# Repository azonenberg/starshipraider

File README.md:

# Intro

This is the umbrella repo for a lot of my T&M projects. Some will end up in separate repos.

# Project Codenames

Boards, subsystems, etc are all named after famous electrical engineers who made major contributions to the field of test equipment design.

# Platform Architecture

All instruments are planned to share the same basic platform. Generally speaking, this platform will be:

## Mechanical form factor

* 1U rackmount, depth dependent on the specific instrument.

## Power
* 48V DC power on 6-pin Molex Mini-Fit Jr connector (back left)
* Intermediate bus converter based on the [trigger crossbar](https://github.com/azonenberg/triggercrossbar/tree/main/pcb/ibc) IBC design to produce 12V output.
* Possible changes from current design (as of 2024-03-31): switch to bigger MCU with flash space for A/B firmware images, consider swapping main DC-DC module to something with lower standby power (current IBC wastes ~3W no-load which isn't great)
* STM32L0 based power/reset sequencing supervisor with soft power on/off

## Software/firmware stack

* ngscopeclient as primary UI
* staticnet as TCP/IP stack
* Bare metal, no OS, no dynamic memory allocation
* SFTP based firmware update, eventually with signed updates (user can add new signing keys via uart console)

## Main chipset
* STM32H7 as main processor running SCPI stack, sshd, and control plane functionality (low speed ADCs/DACs, GPIOs, etc)
* Xilinx UltraScale+ / UltraScale / 7 series FPGA as main datapath. Some instruments may have >1 FPGA.

## Communications

* KSZ9031 based 10/100/1000 baseT fallback Ethernet interface
* 10Gbase-R SFP+ / 25Gbase-R SFP28 interface for primary remote control path
* Twinlan transport, SCPI control plane socket plus bare TCP socket for binary waveform data
* 2.13" monochrome e-ink display with IP/version/status information
* RS232 console on rear panel RJ45 (Cisco pinout)

## RF / signal interface

* Front panel SMA/BNC probe ports. Number of channels dependent on PCB size.
* Rear panel SMA for 10 MHz reference in, level TBD
* May have reference out TBD
* May have PPS in/out TBD
* Rear panel trigger in/out if applicable

# Roadmap (including external repos)

1. [Trigger Crossbar](https://github.com/azonenberg/triggercrossbar)  
Currently in progress. Not planning to make in volume, focus is on prototyping as much of the platform as possible to speed development and de-risk future projects. Prototype assembled, firmware dev in progress.

1. [kup-lulz](https://github.com/azonenberg/misc-devboards/tree/master/kup-lulz): One-off Kintex UltraScale+ test board on OSHPark 4 layers, using a sketchy reballed aliexpress FPGA. Intended as a low-risk validation for UltraScale+ based power, pcb footprint/schematic, and some RTL development. Schematic complete, fine tuning layout.

1. [GROVER](https://github.com/azonenberg/grover): Kintex UltraScale+ based 10/25G BERT. On hold until kup-lulz is brought up and working as it will essentially be a scaled-up version of the same design

1. VOLLUM (Howard Vollum, co-inventor of triggered-sweep oscilloscope)
    - No design progress yet, but can probably leverage some old frontend work. One 6 Gbps AD9213 is in inventory for a scaled down (7 series based) single channel prototype.
    - 2 GHz / 10 Gsps 12 bit oscilloscope, as many channels as I can fit in 1U
    - Per channel: 1x AD9213, frontend, XCAU25P-2FFVB676, 72-bit DDR4 LRDIMM
    - Top level: One more FPGA, details TBD, doing trigger sync and MSO channels
    - Will need to use parallel / bonded serial LVDS for waveform download since all 12 GTYs on the KU25Ps will be used for the JESD204

-----

# Stuff below here is way old and needs to be redone

-----

## General

* STARSHIPRAIDER: umbrella term for the entire project
* CLARKE (Edith Clarke, first female EE professor in USA): the original STARSHIPRAIDER project

## Oscilloscopes

All are 8 channels??

* BLONDEL (Andre-Eugene Blondel, inventor of electromechanical oscillograph) \
  8 bit: 100 MHz / 250 - 500 - 1000 Msps \
  12 bit: 50 MHz / 125 - 250 - 500 Msps \
  4 AFE : 1 HMCAD1520 \
  Two acquisition cards, 4 channels each \
  One XC7A100T-2FGG676 on main board \
  One DDR3 800 SODIMM on main board

* DUDDELL (William Duddell, inventor of moving-coil mirror oscillograph) \
  250 MHz / 1 Gsps, 1 AFE : 1 HMCAD1520
  1x XC7K160T-2FFG676

  Eight analog cards, one HMCAD1520 + one AFE each
  One digital card with 1-2 SFF-8087 connectors for LA
  One AWG card with a TBD JESD204 DAC using unused serdes lanes (assuming 4 for 40G, one for 10G, three available)

* ZENNECK (Jonathan Zenneck, inventor of electrically scanned CRT oscilloscope) \
  500 MHz or 1 GHz / 5 Gsps, 1 AFE : 1 AD9213-6G

  Per channel:
  * 1x XC7A200T-2FFG1156
  * 1x AD9213 in 6G speed grade
  * 2x DDR3 800 SODIMM

  Global:
  * 1x XC7K160T-2FFG160T (could do six channels with direct lane to each one)

* VOLLUM (Howard Vollum, co-inventor of triggered-sweep oscilloscope) \
  1-2 GHz / 10 Gsps, 1 AFE : 1 AD9213

* MURDOCK (Melvin Jack Murdock, co-inventor of triggered-sweep oscilloscope) \
  6 GHz / 40 Gsps, 1 AFE : 4 AD9213

## Probes / peripherals

* CONWAY (VLSI pioneer, co-author of Mead & Conway) \
  8-bit comparator-to-LVDS logic analyzer pod with SFF-8087 interface and high-impedance inputs

* MEAD (other half of Mead & Conway) \
  8-bit comparator-to-LVDS logic analyzer pod with SFF-8087 interface and 50 ohm inputs

* MAXWELL (James Clerk Maxwell, discovered Maxwell's Equations) \
  Kintex-7 ISERDESE2 based LA

* TODO: Artix-7 GTP based LA??

* DENNARD (Robert Dennard, inventor of DRAM) \
  Kintex-7 GTX based LA

* BRAUN (Karl Ferdinand Braun, inventor of optically scanned CRT oscilloscope and phased array)
  Low-bandwidth active probe
	ADA4817-1ACPZ-R7

## Signal Generators

* FLEMING (John Ambrose Fleming, inventor of vacuum tube)
  4 channel 14 bit 2.5 Gsps arbitrary waveform generator, AD9739 + Kintex-7 + DDR3 SODIMM based.
  Need ~160 Gbps of RAM bandwidth to keep them fed

  Two channels of 14-bit LVDS per DAC = 28 LVDS pairs for data, assume clock/sync are external to FPGA
  Slow control: 4 wire SPI, IRQ = 5 slow lines

  4x DAC = 84 pairs (168 pins used / 4 banks / 200 allocated) + 15 slow lines

  Two xc7k160t's, two dacs + 1 sodimm of ram on each

  4GB DDR3 SODIMM, 1 GB per channel = 512 Mpoints of waveform data
  Probably some digital outputs (mix of LVDS and LVCMOS, and maybe some slow pin headers?)

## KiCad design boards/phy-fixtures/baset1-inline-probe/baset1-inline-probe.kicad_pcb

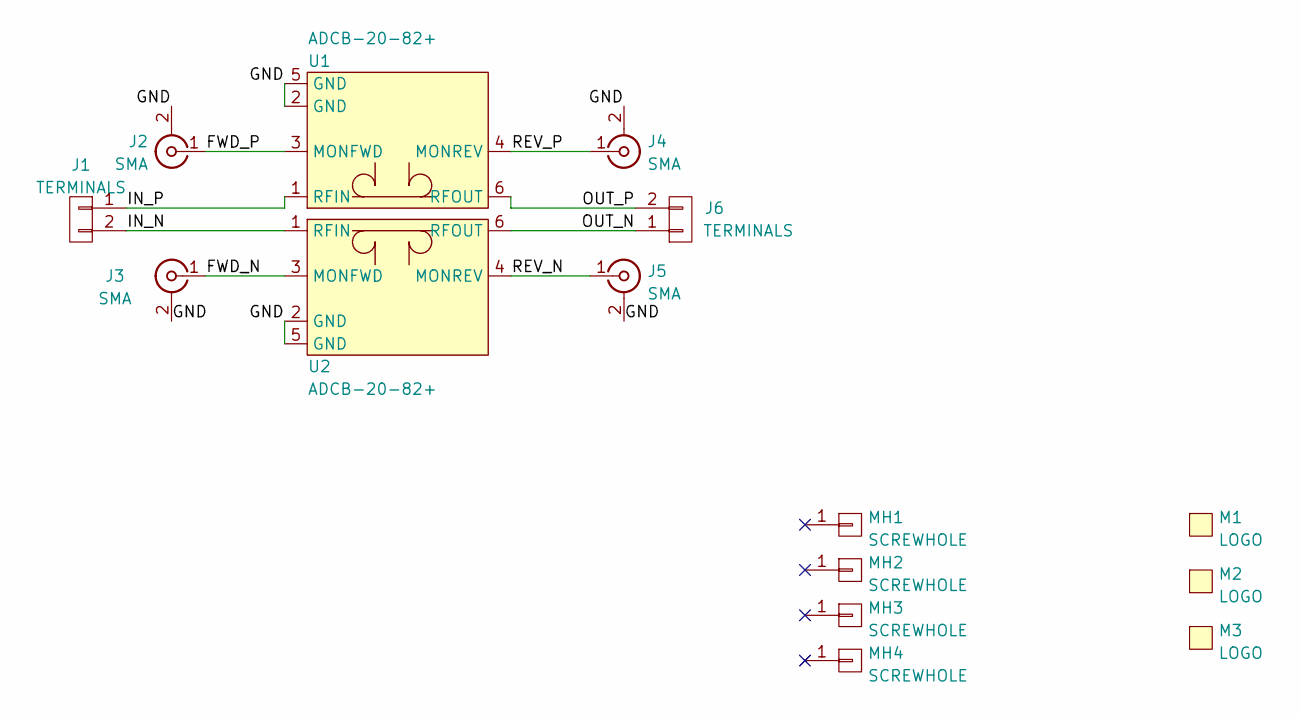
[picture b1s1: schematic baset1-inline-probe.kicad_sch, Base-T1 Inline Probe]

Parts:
J1, J6: TERMINALS; CONN_HEADER_2.54MM_1x2
J2, J3, J4, J5: SMA; CONN_SMA_EDGE_SAMTEC_SMA_J_P_H_ST_EM1
M1: LOGO; LONGTHING-1200DPI
M2: LOGO; Logo_silk_WEEE_3.4x5mm
M3: LOGO; Logo_silk_OSHW_6x6mm
MH1, MH2, MH3, MH4: SCREWHOLE; MECHANICAL_CLEARANCEHOLE_4_40
U1, U2: ADCB-20-82+; COUPLER_MINICIRCUITS_ADCB-20-82+

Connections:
/FWD_N: J3.1 (In), U2.3 (MONFWD)
/FWD_P: J2.1 (In), U1.3 (MONFWD)
/GND: J2.2 (Ext), J3.2 (Ext), J4.2 (Ext), J5.2 (Ext), U1.2 (GND), U1.5 (GND), U2.2 (GND), U2.5 (GND)
/IN_N: J1.2, U2.1 (RFIN)
/IN_P: J1.1, U1.1 (RFIN)
/OUT_N: J6.1, U2.6 (RFOUT)
/OUT_P: J6.2, U1.6 (RFOUT)
/REV_N: J5.1 (In), U2.4 (MONREV)
/REV_P: J4.1 (In), U1.4 (MONREV)

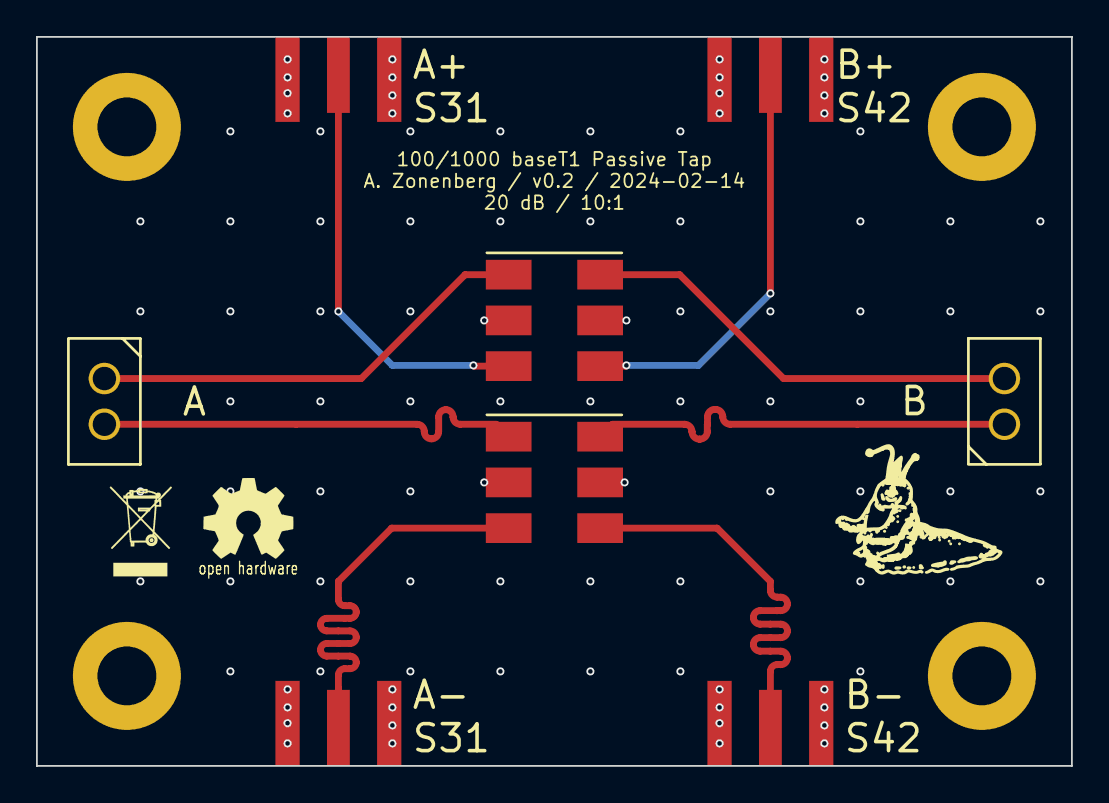
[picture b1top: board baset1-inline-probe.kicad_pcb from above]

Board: 4 copper layers, 57.5 x 40.5 mm, 15 parts (0 on the bottom side), 9 nets.

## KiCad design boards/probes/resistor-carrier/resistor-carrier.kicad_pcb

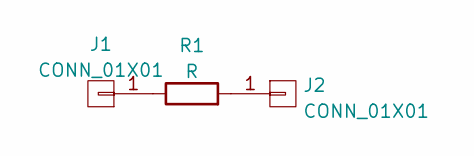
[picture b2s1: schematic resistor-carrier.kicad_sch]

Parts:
J1, J2: CONN_01X01; EDGELAUNCH_350UM
R1: R; EIA_0201_RES_NOSILK

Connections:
unnamed: J1.1, R1.1
unnamed: J2.1, R1.2

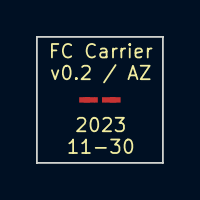
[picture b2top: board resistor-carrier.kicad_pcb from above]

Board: 2 copper layers, 7.0 x 7.0 mm, 3 parts (0 on the bottom side), 2 nets.

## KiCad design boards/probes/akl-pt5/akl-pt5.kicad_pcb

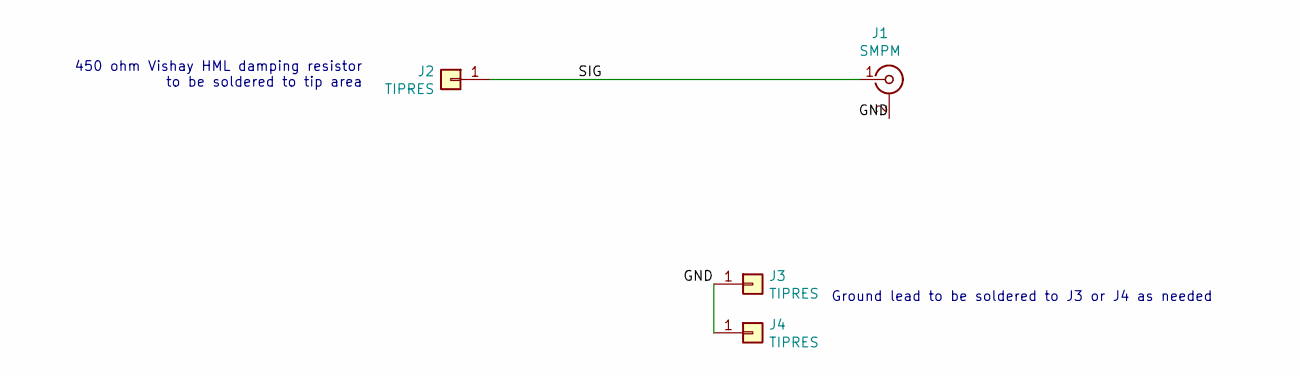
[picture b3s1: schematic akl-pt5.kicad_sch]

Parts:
J1: SMPM; CONN_SMPM_AMPHENOL_925-169J-51PT_SHORT
J2, J3, J4: TIPRES; EDGELAUNCH_350UM

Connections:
/GND: J1.2 (Ext), J3.1, J4.1
/SIG: J1.1 (In), J2.1

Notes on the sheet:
450 ohm Vishay HML damping resistor to be soldered to tip area
Ground lead to be soldered to J3 or J4 as needed

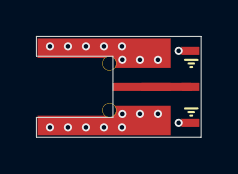
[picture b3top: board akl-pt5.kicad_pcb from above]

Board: 4 copper layers, 9.2 x 5.6 mm, 4 parts (0 on the bottom side), 2 nets.

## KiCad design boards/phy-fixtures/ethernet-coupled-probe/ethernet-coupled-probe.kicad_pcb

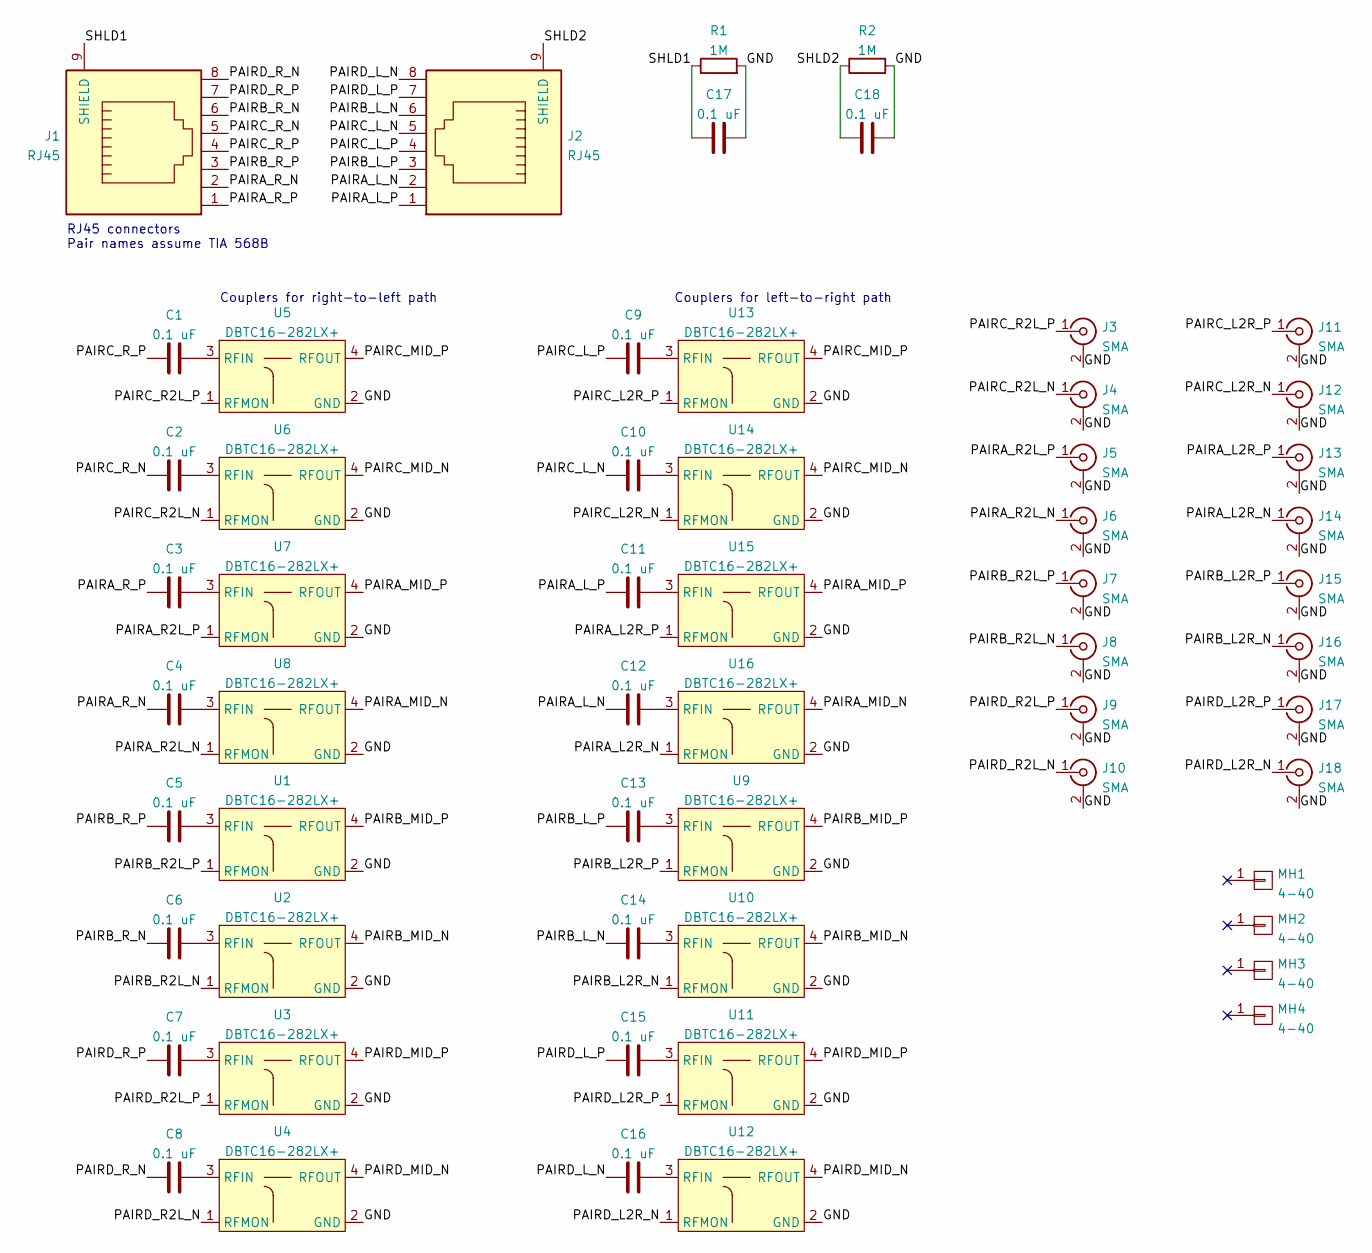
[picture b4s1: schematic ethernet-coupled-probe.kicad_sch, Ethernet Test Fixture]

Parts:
C1, C2, C3, C4, C5, C6, C7, C8, C9, C10, C11, C12, C13, C14, C15, C16, C17, C18: 0.1 uF; EIA_0402_CAP_NOSILK
J1, J2: RJ45; CONN_RJ45_BELSTEWART_SS-7188S-A-PG4-1-BA-xx
J3, J4, J5, J6, J7, J8, J9, J10, J11, J12, J13, J14, J15, J16, J17, J18: SMA; CONN_SMA_EDGE_SAMTEC_SMA_J_P_H_ST_EM1
MH1, MH2, MH3, MH4: 4-40; MECHANICAL_CLEARANCEHOLE_4_40
R1, R2: 1M; EIA_0402_RES_NOSILK
U1, U2, U3, U4, U5, U6, U7, U8, U9, U10, U11, U12, U13, U14, U15, U16: DBTC16-282LX+; COUPLER_MINICIRCUITS_DBTC16-282LX

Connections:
/GND: C17.2, C18.2, J3.2 (Ext), J4.2 (Ext), J5.2 (Ext), J6.2 (Ext), J7.2 (Ext), J8.2 (Ext), J9.2 (Ext), J10.2 (Ext), J11.2 (Ext), J12.2 (Ext), J13.2 (Ext), J14.2 (Ext), J15.2 (Ext), J16.2 (Ext), J17.2 (Ext), J18.2 (Ext), R1.2, R2.2, U1.2 (GND), U2.2 (GND), U3.2 (GND), U4.2 (GND), U5.2 (GND), U6.2 (GND), U7.2 (GND), U8.2 (GND), U9.2 (GND), U10.2 (GND), U11.2 (GND), U12.2 (GND), U13.2 (GND), U14.2 (GND), U15.2 (GND), U16.2 (GND)
/PAIRA_L2R_N: J14.1 (In), U16.1 (RFMON)
/PAIRA_L2R_P: J13.1 (In), U15.1 (RFMON)
/PAIRA_L_N: C12.1, J2.2
/PAIRA_L_P: C11.1, J2.1
/PAIRA_MID_N: U8.4 (RFOUT), U16.4 (RFOUT)
/PAIRA_MID_P: U7.4 (RFOUT), U15.4 (RFOUT)
/PAIRA_R2L_N: J6.1 (In), U8.1 (RFMON)
/PAIRA_R2L_P: J5.1 (In), U7.1 (RFMON)
/PAIRA_R_N: C4.1, J1.2
/PAIRA_R_P: C3.1, J1.1
/PAIRB_L2R_N: J16.1 (In), U10.1 (RFMON)
/PAIRB_L2R_P: J15.1 (In), U9.1 (RFMON)
/PAIRB_L_N: C14.1, J2.6
/PAIRB_L_P: C13.1, J2.3
/PAIRB_MID_N: U2.4 (RFOUT), U10.4 (RFOUT)
/PAIRB_MID_P: U1.4 (RFOUT), U9.4 (RFOUT)
/PAIRB_R2L_N: J8.1 (In), U2.1 (RFMON)
/PAIRB_R2L_P: J7.1 (In), U1.1 (RFMON)
/PAIRB_R_N: C6.1, J1.6
/PAIRB_R_P: C5.1, J1.3
/PAIRC_L2R_N: J12.1 (In), U14.1 (RFMON)
/PAIRC_L2R_P: J11.1 (In), U13.1 (RFMON)
/PAIRC_L_N: C10.1, J2.5
/PAIRC_L_P: C9.1, J2.4
/PAIRC_MID_N: U6.4 (RFOUT), U14.4 (RFOUT)
/PAIRC_MID_P: U5.4 (RFOUT), U13.4 (RFOUT)
/PAIRC_R2L_N: J4.1 (In), U6.1 (RFMON)
/PAIRC_R2L_P: J3.1 (In), U5.1 (RFMON)
/PAIRC_R_N: C2.1, J1.5
/PAIRC_R_P: C1.1, J1.4
/PAIRD_L2R_N: J18.1 (In), U12.1 (RFMON)
/PAIRD_L2R_P: J17.1 (In), U11.1 (RFMON)
/PAIRD_L_N: C16.1, J2.8
/PAIRD_L_P: C15.1, J2.7
/PAIRD_MID_N: U4.4 (RFOUT), U12.4 (RFOUT)
/PAIRD_MID_P: U3.4 (RFOUT), U11.4 (RFOUT)
/PAIRD_R2L_N: J10.1 (In), U4.1 (RFMON)
/PAIRD_R2L_P: J9.1 (In), U3.1 (RFMON)
/PAIRD_R_N: C8.1, J1.8
/PAIRD_R_P: C7.1, J1.7
/SHLD1: C17.1, J1.9 (SHIELD), R1.1
/SHLD2: C18.1, J2.9 (SHIELD), R2.1
unnamed: C1.2, U5.3 (RFIN)
unnamed: C2.2, U6.3 (RFIN)
unnamed: C3.2, U7.3 (RFIN)
unnamed: C4.2, U8.3 (RFIN)
unnamed: C5.2, U1.3 (RFIN)
unnamed: C6.2, U2.3 (RFIN)
unnamed: C7.2, U3.3 (RFIN)
unnamed: C8.2, U4.3 (RFIN)
unnamed: C9.2, U13.3 (RFIN)
unnamed: C10.2, U14.3 (RFIN)
unnamed: C11.2, U15.3 (RFIN)
unnamed: C12.2, U16.3 (RFIN)
unnamed: C13.2, U9.3 (RFIN)
unnamed: C14.2, U10.3 (RFIN)
unnamed: C15.2, U11.3 (RFIN)
unnamed: C16.2, U12.3 (RFIN)

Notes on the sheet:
Couplers for left-to-right path
Couplers for right-to-left path
RJ45 connectors Pair names assume TIA 568B

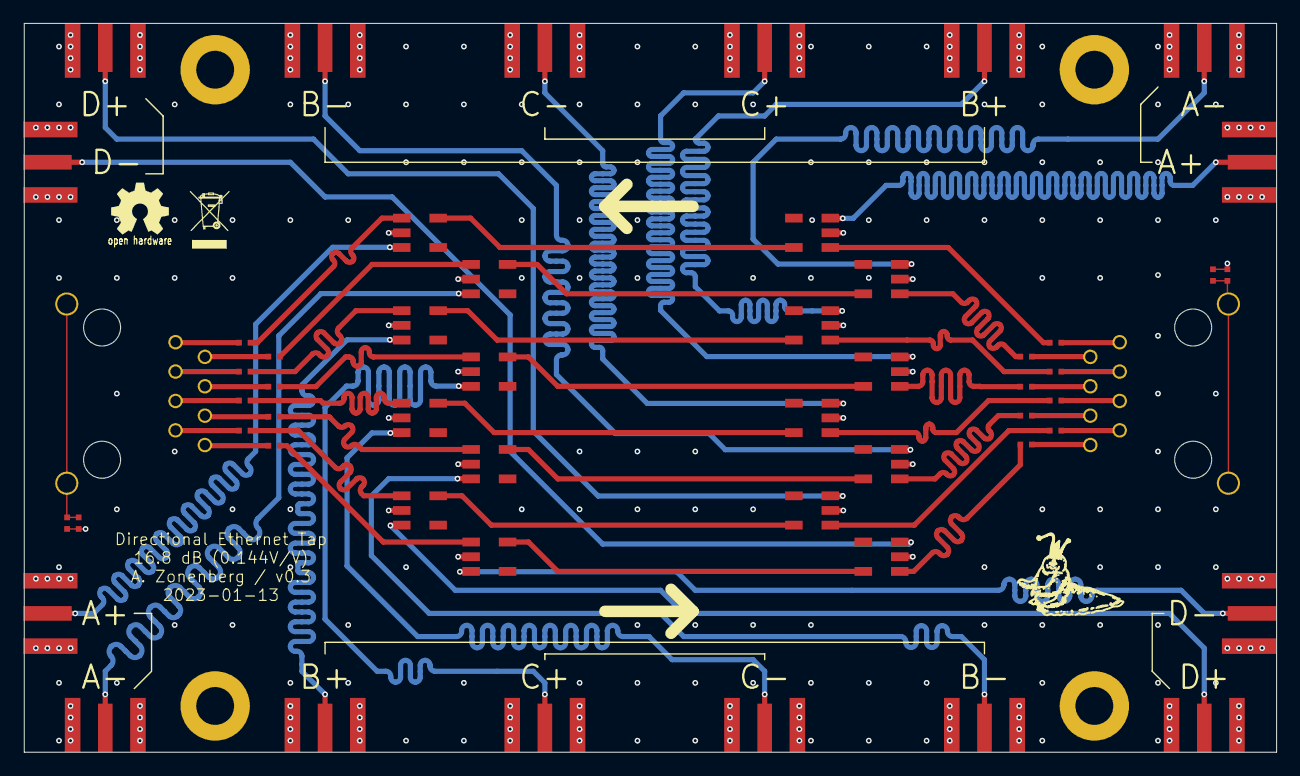
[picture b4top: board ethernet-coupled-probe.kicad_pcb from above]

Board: 4 copper layers, 108.2 x 63.0 mm, 58 parts (1 on the bottom side), 59 nets.

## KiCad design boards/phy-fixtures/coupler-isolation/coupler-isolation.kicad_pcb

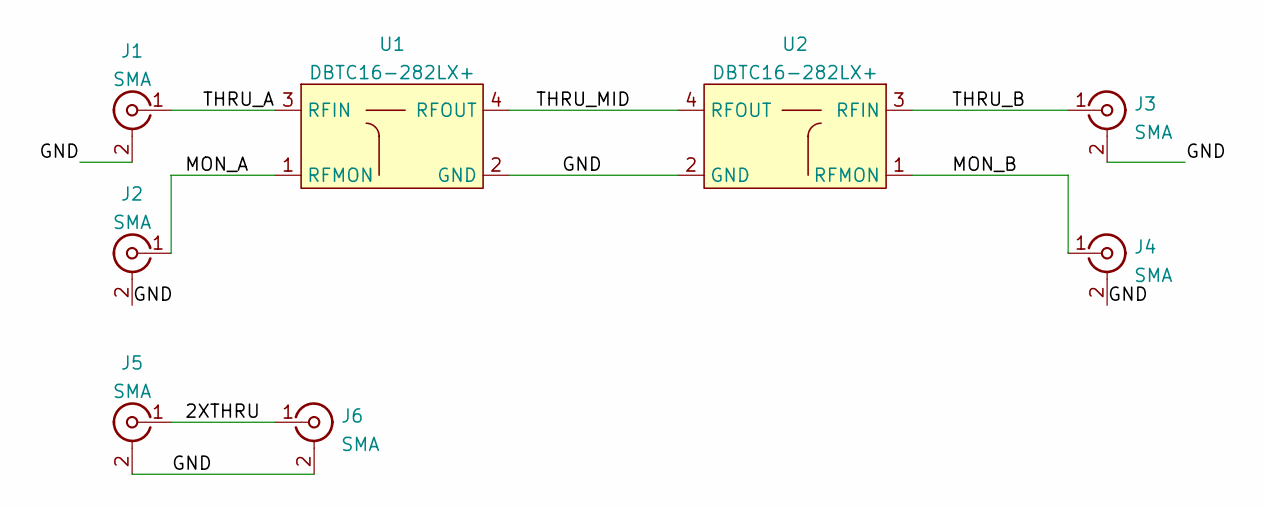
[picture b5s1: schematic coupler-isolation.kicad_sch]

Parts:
J1, J2, J3, J4, J5, J6: SMA; CONN_SMA_EDGE_SAMTEC_SMA_J_P_H_ST_EM1
U1, U2: DBTC16-282LX+; COUPLER_MINICIRCUITS_DBTC16-282LX

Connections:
/2XTHRU: J5.1 (In), J6.1 (In)
/GND: J1.2 (Ext), J2.2 (Ext), J3.2 (Ext), J4.2 (Ext), J5.2 (Ext), J6.2 (Ext), U1.2 (GND), U2.2 (GND)
/MON_A: J2.1 (In), U1.1 (RFMON)
/MON_B: J4.1 (In), U2.1 (RFMON)
/THRU_A: J1.1 (In), U1.3 (RFIN)
/THRU_B: J3.1 (In), U2.3 (RFIN)
/THRU_MID: U1.4 (RFOUT), U2.4 (RFOUT)

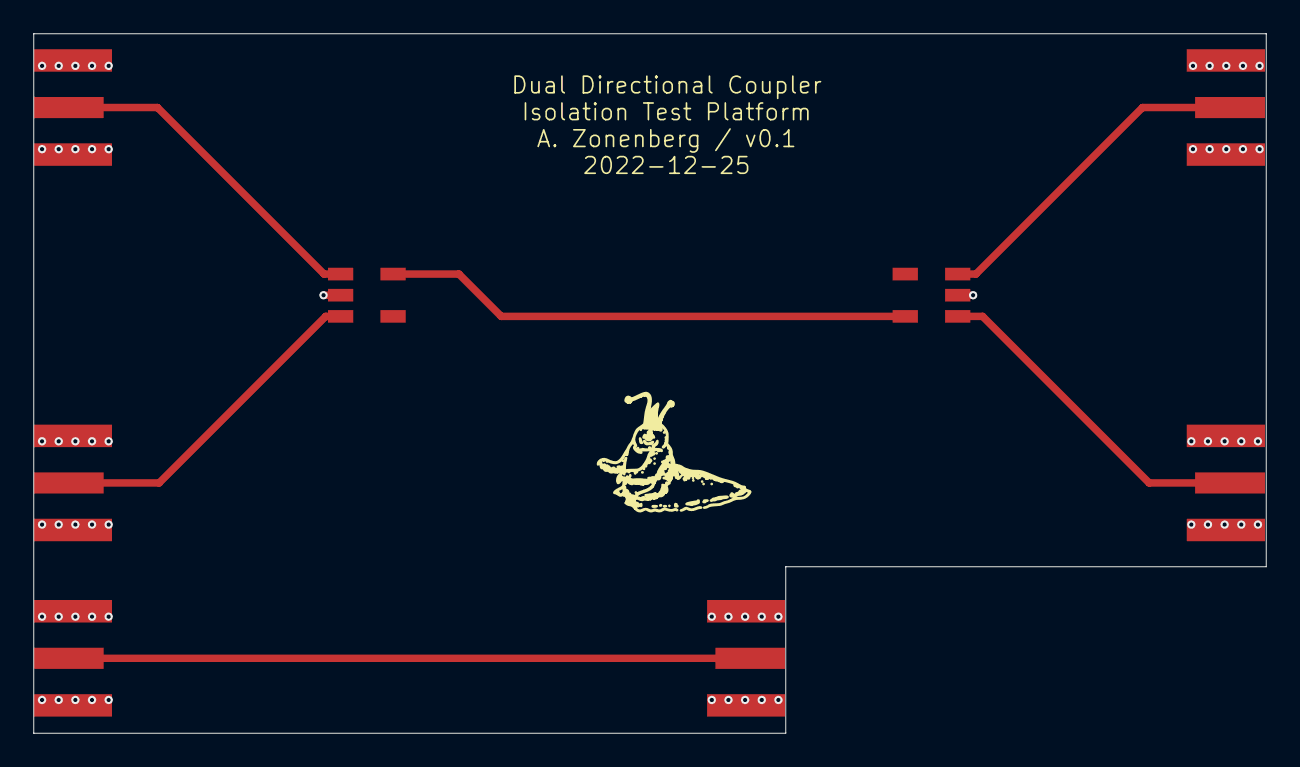
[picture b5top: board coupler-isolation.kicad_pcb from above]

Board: 4 copper layers, 74.0 x 42.0 mm, 8 parts (0 on the bottom side), 7 nets.

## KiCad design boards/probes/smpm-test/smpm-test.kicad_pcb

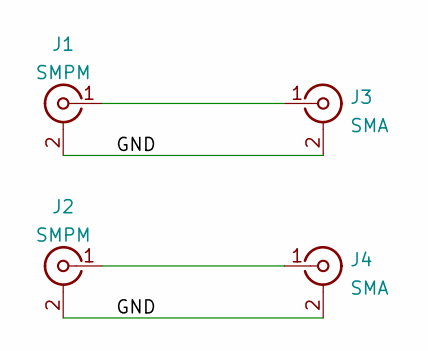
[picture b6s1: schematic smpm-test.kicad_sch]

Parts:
J1, J2: SMPM; CONN_SMPM_AMPHENOL_925-169J-51PT_SHORT
J3, J4: SMA; CONN_SMA_EDGE_ROSENBERGER_32K243_40ML5

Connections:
/GND: J1.2 (Ext), J2.2 (Ext), J3.2 (Ext), J4.2 (Ext)
unnamed: J1.1 (In), J3.1 (In)
unnamed: J2.1 (In), J4.1 (In)

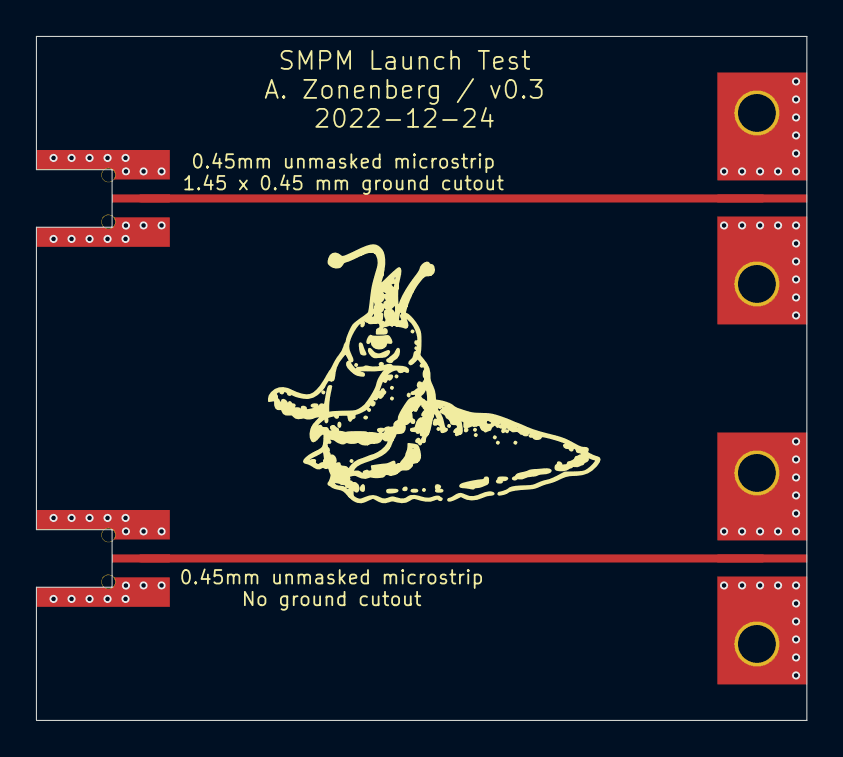
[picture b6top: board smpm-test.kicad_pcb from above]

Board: 4 copper layers, 42.8 x 38.0 mm, 4 parts (0 on the bottom side), 3 nets.

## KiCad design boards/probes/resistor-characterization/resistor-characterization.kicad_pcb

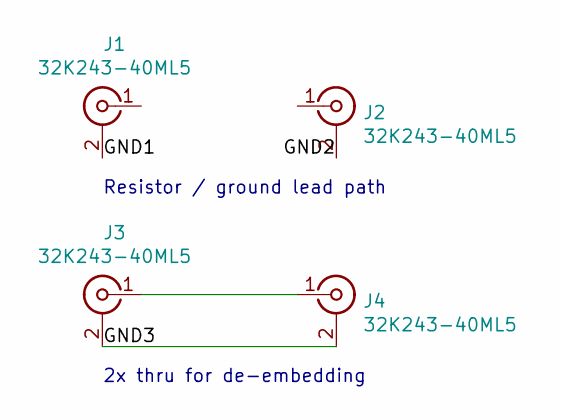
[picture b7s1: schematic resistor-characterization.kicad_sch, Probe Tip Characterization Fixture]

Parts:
J1, J2, J3, J4: 32K243-40ML5; CONN_SMA_EDGE_ROSENBERGER_32K243_40ML5

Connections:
/GND1: J1.2 (Ext)
/GND2: J2.2 (Ext)
/GND3: J3.2 (Ext), J4.2 (Ext)
unnamed: J3.1 (In), J4.1 (In)

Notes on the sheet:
2x thru for de-embedding
Resistor / ground lead path

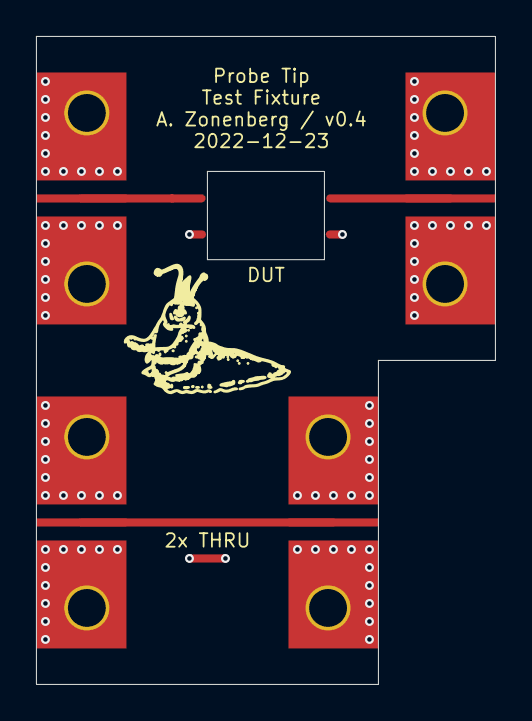
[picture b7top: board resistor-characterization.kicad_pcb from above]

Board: 4 copper layers, 25.5 x 36.0 mm, 4 parts (0 on the bottom side), 2 nets.

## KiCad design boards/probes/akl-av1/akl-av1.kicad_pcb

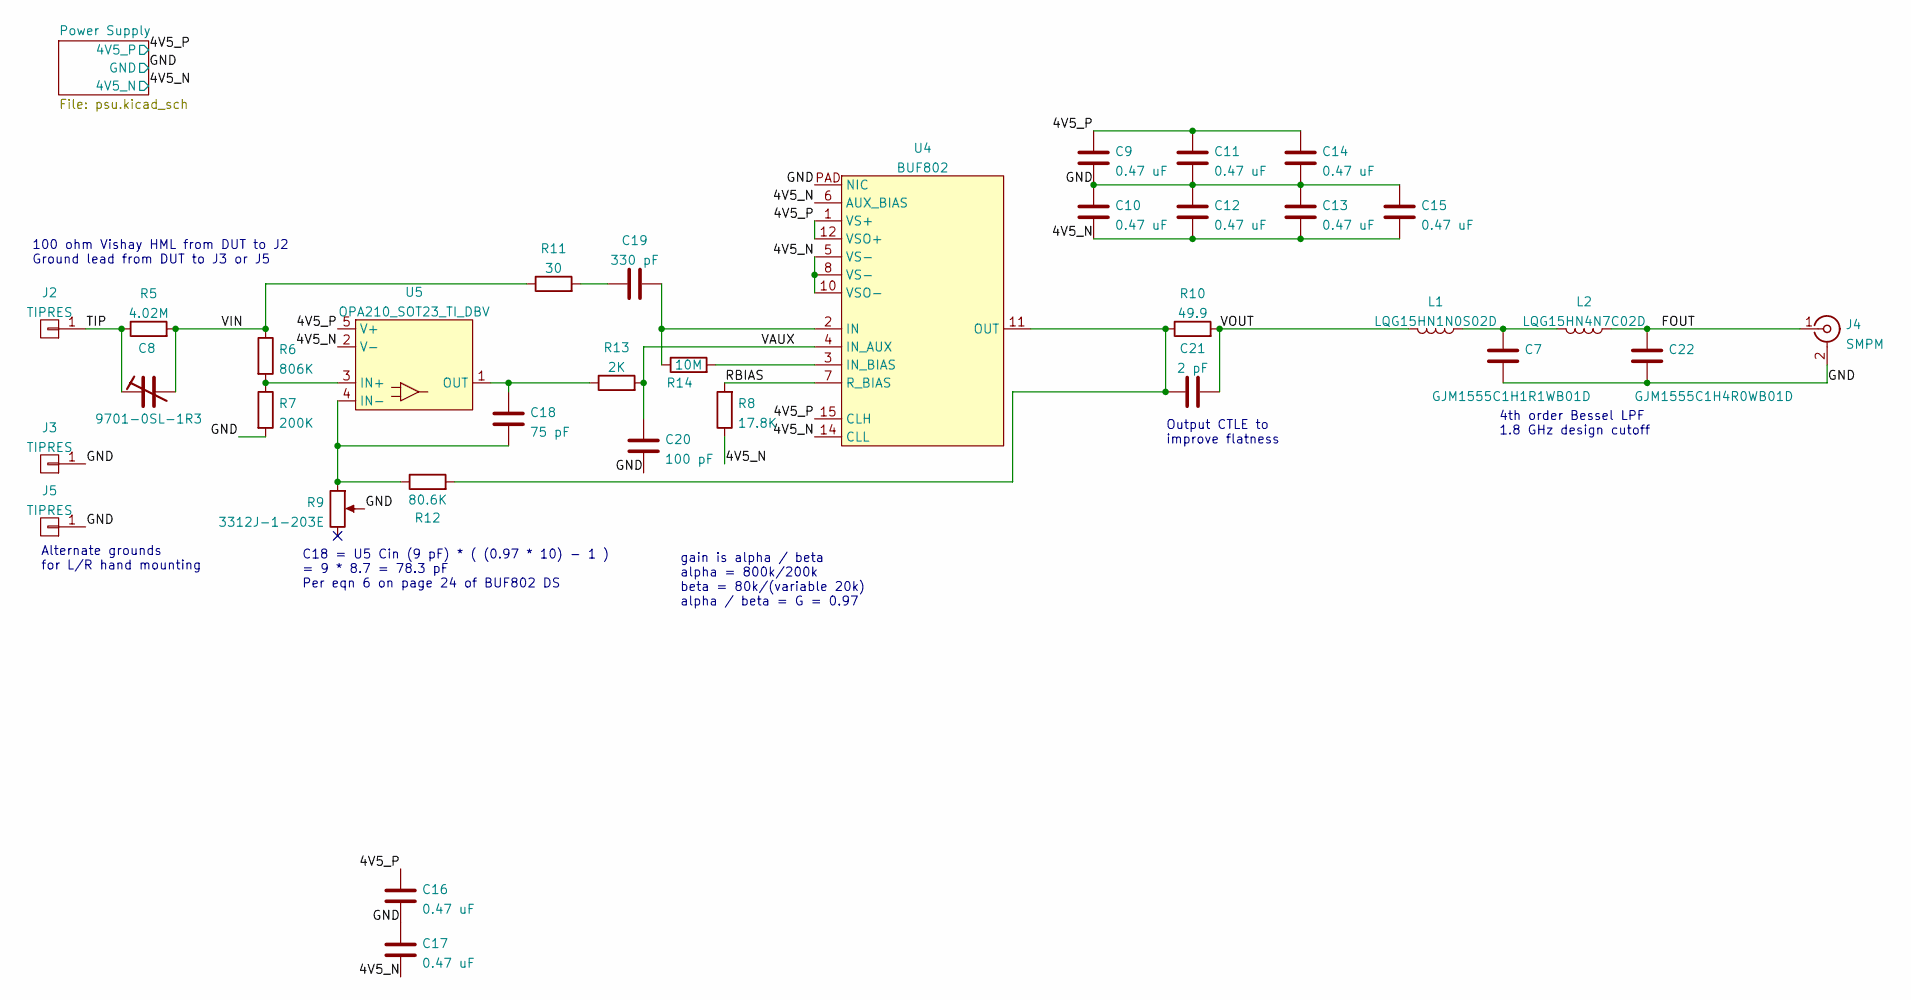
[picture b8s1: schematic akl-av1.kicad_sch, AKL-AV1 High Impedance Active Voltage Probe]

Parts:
C7: GJM1555C1H1R1WB01D; EIA_0402_CAP_NOSILK
C8: 9701-0SL-1R3; CAP_TRIM_KNOWLES_9701_xSL-1
C9, C10, C11, C12, C13, C14, C15, C16, C17: 0.47 uF; EIA_0402_CAP_NOSILK
C18: 75 pF; EIA_0402_CAP_NOSILK
C19: 330 pF; EIA_0402_CAP_NOSILK
C20: 100 pF; EIA_0402_CAP_NOSILK
C21: 2 pF; EIA_0402_CAP_NOSILK
C22: GJM1555C1H4R0WB01D; EIA_0402_CAP_NOSILK
J2, J3, J5: TIPRES; EDGELAUNCH_350UM
J4: SMPM; CONN_SMPM_AMPHENOL_925-169J-51PT_SHORT
L1: LQG15HN1N0S02D; EIA_0402_CAP_NOSILK
L2: LQG15HN4N7C02D; EIA_0402_CAP_NOSILK
R5: 4.02M; EIA_0402_RES_NOSILK
R6: 806K; EIA_0402_RES_NOSILK
R7: 200K; EIA_0402_RES_NOSILK
R8: 17.8K; EIA_0402_RES_NOSILK
R9: 3312J-1-203E; RES_TRIM_BOURNS_3312
R10: 49.9; EIA_0402_RES_NOSILK
R11: 30; EIA_0402_RES_NOSILK
R12: 80.6K; EIA_0402_RES_NOSILK
R13: 2K; EIA_0402_RES_NOSILK
R14: 10M; EIA_0402_RES_NOSILK
U4: BUF802; QFN_16_0.5MM_3x3MM
U5: OPA210_SOT23_TI_DBV; SOT23_5

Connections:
/4V5_N: C10.2, C12.2, C13.2, C15.2, C17.2, R8.1, U4.5 (VS-), U4.6 (AUX_BIAS), U4.8 (VS-), U4.10 (VSO-), U4.14 (CLL), U5.2 (V-); also elsewhere on the board
/4V5_P: C9.1, C11.1, C14.1, C16.1, U4.1 (VS+), U4.12 (VSO+), U4.15 (CLH), U5.5 (V+); also elsewhere on the board
/FOUT: C22.2, J4.1 (In), L2.1
/GND: C7.1, C9.2, C10.1, C11.2, C12.1, C13.1, C14.2, C15.1, C16.2, C17.1, C20.2, C22.1, J3.1, J4.2 (Ext), J5.1, R7.2, R9.2, U4.PAD (NIC); also elsewhere on the board
/RBIAS: R8.2, U4.7 (R_BIAS)
/TIP: C8.1, J2.1, R5.1
/VAUX: C20.1, R13.2, U4.4 (IN_AUX)
/VIN: C8.2, R5.2, R6.1, R11.1
/VOUT: C21.2, L1.2, R10.2
unnamed: C7.2, L1.1, L2.2
unnamed: C18.1, R9.1, R12.1, U5.4 (IN-)
unnamed: C18.2, R13.1, U5.1 (OUT)
unnamed: C19.1, R11.2
unnamed: C19.2, R14.1, U4.2 (IN)
unnamed: C21.1, R10.1, R12.2, U4.11 (OUT)
unnamed: R6.2, R7.1, U5.3 (IN+)
unnamed: R14.2, U4.3 (IN_BIAS)

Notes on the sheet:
C18 = U5 Cin (9 pF) * ( (0.97 * 10) - 1 ) = 9 * 8.7 = 78.3 pF Per eqn 6 on page 24 of BUF802 DS
Output CTLE to improve flatness
Alternate grounds for L/R hand mounting
gain is alpha / beta alpha = 800k/200k beta = 80k/(variable 20k) alpha / beta = G = 0.97
4th order Bessel LPF 1.8 GHz design cutoff
100 ohm Vishay HML from DUT to J2 Ground lead from DUT to J3 or J5

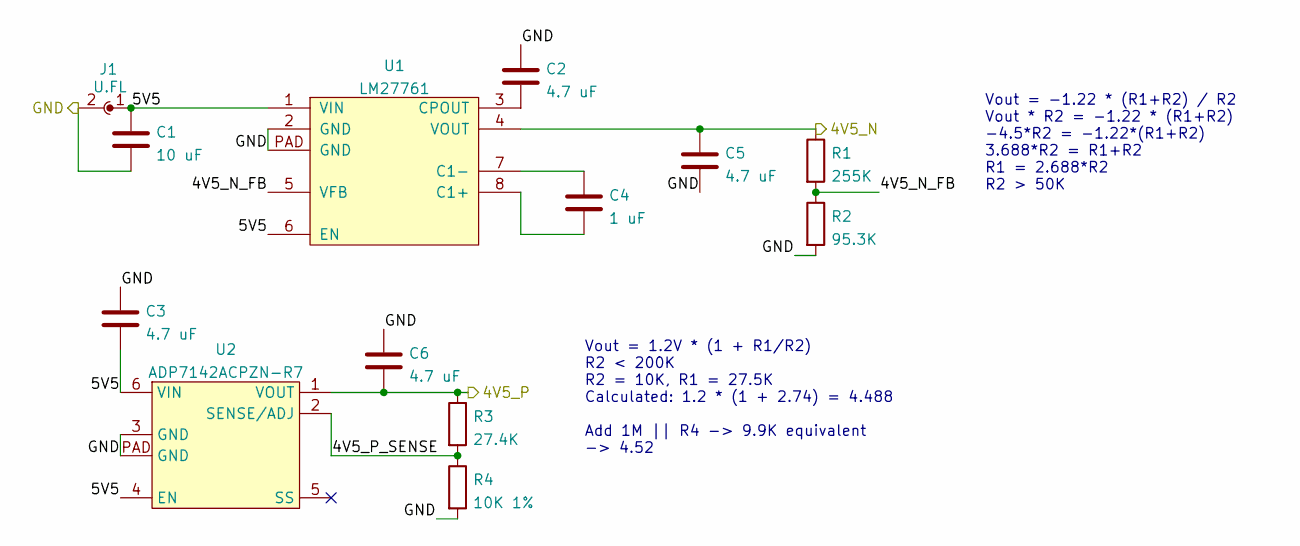
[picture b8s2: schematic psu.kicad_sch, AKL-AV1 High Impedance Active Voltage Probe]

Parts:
C1: 10 uF; EIA_0805_CAP_NOSILK
C2, C3, C5, C6: 4.7 uF; EIA_0603_CAP_NOSILK
C4: 1 uF; EIA_0603_CAP_NOSILK
J1: U.FL; CONN_U.FL_TE_1909763-1
R1: 255K; EIA_0402_RES_NOSILK
R2: 95.3K; EIA_0402_RES_NOSILK
R3: 27.4K; EIA_0402_RES_NOSILK
R4: 10K 1%; EIA_0402_RES_NOSILK
U1: LM27761; DFN_8_0.5MM_2x2MM
U2: ADP7142ACPZN-R7; DFN_6_0.65MM_2x2MM

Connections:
/4V5_N: C5.1, R1.1, U1.4 (VOUT); also elsewhere on the board
/4V5_P: C6.2, R3.1, U2.1 (VOUT); also elsewhere on the board
/GND: C1.2, C2.1, C3.1, C5.2, C6.1, J1.2, R2.2, R4.2, U1.2 (GND), U1.PAD (GND), U2.3 (GND), U2.PAD (GND); also elsewhere on the board
/Power Supply/4V5_N_FB: R1.2, R2.1, U1.5 (VFB)
/Power Supply/4V5_P_SENSE: R3.2, R4.1, U2.2 (SENSE/ADJ)
/Power Supply/5V5: C1.1, C3.2, J1.1, U1.1 (VIN), U1.6 (EN), U2.4 (EN), U2.6 (VIN)
unnamed: C2.2, U1.3 (CPOUT)
unnamed: C4.1, U1.7 (C1-)
unnamed: C4.2, U1.8 (C1+)

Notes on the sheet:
Vout = 1.2V * (1 + R1/R2) R2 < 200K R2 = 10K, R1 = 27.5K Calculated: 1.2 * (1 + 2.74) = 4.488 Add 1M || R4 -> 9.9K equivalent -> 4.52
Vout = -1.22 * (R1+R2) / R2 Vout * R2 = -1.22 * (R1+R2) -4.5*R2 = -1.22*(R1+R2) 3.688*R2 = R1+R2 R1 = 2.688*R2 R2 > 50K

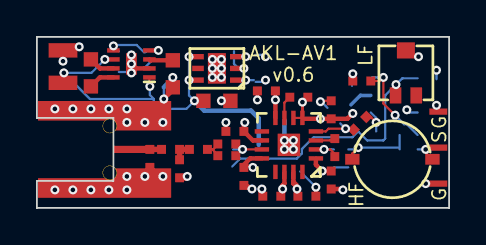
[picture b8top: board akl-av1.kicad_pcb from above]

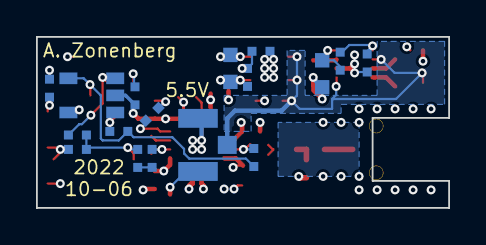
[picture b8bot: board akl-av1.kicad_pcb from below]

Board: 4 copper layers, 22.9 x 9.5 mm, 47 parts (17 on the bottom side), 23 nets.

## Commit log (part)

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2020-06-20 Changed comparators on GTX inputs to ADCMP582s, added pins for 0V5 supply
2020-06-20 Added 0.5V Vtt rail
2020-06-21 Added ferrites to 12V power outputs to improve EMC performance. Fixed incorrect 1V0 hookup for small FPGA. Fixed some other ERC errors
2020-06-21 Added four I2C temp sensors, plus INA233 for 12V0 rail
2020-06-22 Continued work on schematic review
2020-06-22 Fixed LCD backlight polarity reversed. Added pulldowns instead of direct ground connections to SODIMM unused rank chip select/clock
2020-06-22 Fixed missing AA16 ground on U2C symbol
2020-06-22 Assigned footprints for all capacitors
2020-06-22 Added four debug indicator LEDs to STM32
2020-06-23 Continued schematic review. Finished verifying pinouts. Assigned lots more footprints.
2020-06-23 Continued assigning footprints. Done with everything up to and not including resistors.
2020-06-23 Began assigning IC footprints
2020-06-23 Added footprints for everything but LCD
2020-06-23 Added mounting holes and fiducials to top level schematic page
2020-06-24 Added missing AC coupling cap on OCXO output
2020-06-24 Changed OCXO output termination to series instead of parallel
2020-06-24 Continued schematic review
2020-06-24 Added 2 pin header to VBAT rail for optional external battery
2020-06-24 Added polyfuses on 12V0 rails for fans
2020-06-25 Continued design review, finished power portion
2020-06-25 Deleted pulldowns on EN signals as these are redundant
2020-06-25 Added mechanical footprints for fans etc
2020-06-25 Added pullups to I2C1/2
2020-06-25 Added extra bulk capacitance to Vtt rail near SODIMM
2020-06-25 Added 100 ohm terminator to VCO LVDS output
2020-06-25 Continued design review. Added pulldowns to various power rail enables. Fixed pulls to on instead of off on active-low power rail enables.
2020-06-25 Added missing series resistors to RJ45 LEDs
2020-06-25 Initial PCB with all components after review
2020-06-25 Initial stackup simulations for MAXWELL
2020-06-26 Continued stackup design
2020-06-26 Added an extra 0.47 uF decoupling cap to Ethernet PHY 3V3 rail. Initial layout of PHY area.
2020-06-26 Routed QSFP+ power
2020-06-26 Fanout of first few probe connectors
2020-06-26 Initial routing of right 5 pods
2020-06-30 Continued layout of pod power switching/monitoring. Initial placement and ground hookups of LCD header.
2020-07-01 Added decoupling caps to Vtt rail on U37. Initial routing of PPS and external trigger inputs.
2020-07-01 Initial routing on refclk comparator
2020-07-02 Initial routing of 12V0 and 3V3_SB power supplies
2020-07-04 Initial FPGA design for MEAD bringup
2020-07-05 Initial temp sensor and LCD bootup support
2020-07-05 Routed backlight power, remaining pod power, setup for MCU
2020-07-06 Final v1.0 probe design for production run
2020-07-06 Moved input connector hole down. Increased wall thickness from 1 mm to 2 mm. Removed dead space at front side of enclosure.
2020-07-06 Increased floor thickness from 1.5 to 2 mm
2020-07-06 Added stiffener ribs to underside of lid
2020-07-06 Continued MCU/LCD layout
2020-07-06 LCD now includes thermal readings for debugging, and includes initial channel name text
2020-07-07 Changed font from 8x16 to 8x15 so we can fit 16 rows of text on the display
2020-07-07 Updated submodules
2020-07-07 AMG240160P: added ClearRow()
2020-07-07 Can now read pod temperatures via the "t" command
2020-07-07 Continued MCU region layout. Rough placement of PSU components near associated regulators.
2020-07-08 Continued MCU layout
2020-07-08 Added LA etc to mead-bringup FPGA image
2020-07-08 Initial skeleton of pod FPGA design
2020-07-08 Fixed bugs causing some channels to be optimized out
2020-07-08 Initial placement and power routing on I/O FPGA
2020-07-08 Initial routing from I/O FPGA to rightmost 2 probe pods
2020-07-09 Finished routing of main power supply area
2020-07-09 Fully routed right half of pod FPGA
2020-07-09 More layout on rightmost pods. Moved main FPGA+RAM to (hopefully) final placement.
2020-07-10 Routing of LVDS data lines for pods 9-7
2020-07-10 Initial routing of DDR3 address/control
2020-07-10 Routed a good chunk of the left side of the RAM
2020-07-10 Routed most of pod 10/11 data interfaces, GTX_1V8 rail, Kintex JTAG
2020-07-11 Finished preliminary routing of pod FPGA
2020-07-11 Updated ipcores
2020-07-12 Initial optimization of DDR byte groups 0-2
2020-07-13 Finished initial length matching of last DQ group
2020-07-14 Continued RAM length matching. A2 is too short but everything else is done!
2020-07-15 Added lockfiles to gitignore
2020-07-15 More SI sims for MAXWELL
2020-07-15 Began routing pod 6
2020-07-16 Hooked up all remaining input signals on the front/back layers. Not length/skew matched yet. Still have to do inner layer stuff.
2020-07-17 Updating file: maxwell-main.kicad_pcb with current fully routed design.
2020-07-17 Continued power plane layout on layer 4
2020-07-18 Began work on initial MAXWELL HDL skeleton
2020-07-18 Continued initial HDL work on MAXWELL. Set up preliminary timing constraints, two trigger deserialization blocks not going anywhere yet.
2020-07-19 Initial SPME implementation, lightly tested in simulation
2020-07-19 Initial implementation of PPME
2020-07-20 Removed BSP stuff as we're not building anything with Splash
2020-07-21 Finished power plane layout on in3. Still have to finish in4 and do some via tweaks etc.
2020-07-21 Length matching of pod 0-9 inputs. 10/11 still have to be done, some ERC errors in meanders.
2020-07-22 Continued work on register interface formal verification. Added actual board delay values to LowSpeedInputs.
2020-07-31 Continued work on probe manual
2020-07-31 Fixed page break
2020-08-03 Final MEAD design package for initial production run
2020-08-16 Updated attenuator-test board with new, closer resistor spacing for v0.2
2020-08-16 Started v1.1 probe design with closely spaced resistors
2020-08-30 New attenuator test rev with 5 resistors
2020-08-30 Attenuator test with 3 resistors
2020-09-12 More simulations of probe effects
2020-09-12 Added filter to v1.2 probe to cancel out peaking from tip. Moved resistors 400um closer to tip.
2020-10-02 v1.3 probe layout
2020-10-04 MAXWELL simulations
2020-10-04 Updated ignores
2020-10-05 Initial version of AKL-PT2 enclosure
2020-10-05 v0.3 AKL-PT2 layout
2020-10-07 Initial AKL-PT3 prototype
2020-10-20 v0.2 AKL-PT2 shell
2020-10-20 Simulations for AKL-PT2
2020-11-16 Initial implementation of multilane CRC simulation
2020-11-17 Removed redundant simulation for architecture that never got used
2020-11-26 Updated simulations for probes
2020-12-15 Initial version of AKL-PT2 bracket
2020-12-23 Fixed nonexistent layer mentioned in fab notes
2020-12-25 Renamed "resistive-probe" filenames to "AKL-PT2". Added new, snugger fit version of probe clip
2020-12-27 Updated AKL-PD1 design with SMPM
2020-12-27 Initial AKL-AD1 schematic (no design review yet)
2020-12-28 Final v0.1 AKL-PD1 layout for prototype
2020-12-29 Basic progress on active probe host side
2021-01-02 active-host-test: went through layout checklist, last minute tidy-ups
2021-01-03 save state with most of the fixes - likely moving to USB PD so FPGA not required
2021-01-03 Updated la-pod-mmcx with larger MMCX cutouts
2021-01-04 active-host-test: layout finished, need to do DRC and follow checklist
2021-01-04 active-host-test: addressed issues found by HardKrash
    - fixed MOSFET drain/source swap
    - switched to FTDI-compatible UART pinout
    - Sized TVS diodes more appropriately.
2021-01-05 v0.3 AKL-PT2 mounting bracket
2021-01-14 active-probe-test: finished base schematic
    TODO is part selection and layout
2021-01-14 active-probe-test: finish component selection
    Also fixed some issues with components on the host
2021-01-20 AKL-PT2: v0.3 mold
2021-01-24 AKL-AD1 v0.2
2021-01-24 Updating MAXWELL power spreadsheet
2021-01-24 Adding a couple of experimental sims for future AKL-AD1 designs
2021-01-24 Updated AKL-PT1 manual
2021-02-05 Updated simulations
2021-02-05 Initial AKL-AD1 firmware
2021-02-13 Removed a bunch of really old sims that don't apply to current hardware
2021-02-13 Removed more obsolete sims
2021-02-18 Added more AKL-PT1 sims
2021-02-19 Continued push-pull port sims of left side area with ENIG
2021-03-02 Lots more AKL-PT1 simulation work
2021-03-04 Added missing via
2021-03-15 Updated enclosure design with new drills
2021-03-20 Moved terminating resistor so we don't have vias in pads
2021-04-01 Initial release of AKL-PT2 datasheet/manual
2021-04-15 SMA test simulations
2021-05-08 Final version of sma-test board for fab
2021-05-25 Initial schematic and layout for AKL-AD3 amplifier board
2021-06-07 Initial version of AKL-AD3 tip
2021-07-05 Updated AKL-AD3 tip with 45 deg tip angle
2021-08-15 Updated AKL-AD3 amplifier and ignore properties
2021-08-15 Added lots of probe simulations
2021-09-01 Rev 0.2 of AKL-AD3 amplifier
2021-09-01 Added Sonnet tech files for sma-test board
2021-09-01 Updated tip with correct copper pours. Bumped version number to v0.3 to disambiguate some mistyped numbers before.
2021-09-01 Fixed a few DFM issues found by Shapeways
2021-09-05 Updated 901-10510-2 with latest footprint from library. Added more vias to connector field
2021-09-26 Updated AKL-AD3 amplifier with proper ground plane *derp*
2021-09-27 v0.4 of top shield
2021-09-28 Removed old single ended sim
2021-10-08 Removed a bunch of sims we don't need anymore
2021-11-26 Added a bunch of AKL-AD3 simulations
2021-11-26 Added OpenOCD configuration for MEAD firmware
2021-11-26 MAXWELL: updated cache config etc for KiCAD 5.1.9
2021-11-26 Updated AKL-PT1 fab notes to specify FR408HR and new directory name
2021-11-26 Added AKL-PT2 test fixture files
2021-11-26 New section in BLONDEL design notes
2021-11-26 Updated MEAD test firmware Vivado project
2021-11-26 Added a bunch of AKL-PT5 simulations
2021-12-26 BNC test: cleared bottom soldermask on trace
2021-12-29 Initial version of vna-amplifier board
2021-12-29 Work on AKL-PT5 v0.2
2022-02-06 Initial version of tip-holder-base
2022-02-06 Initial version of tip-holder
2022-02-20 AKL-PT5 v0.4 layout with bottom side solder pad for tip mounting bracket
2022-03-03 Updated AKL-PT5 layout with floating mounting pad
2022-03-21 Updated silkscreen text
2022-05-27 Updates for KiCAD v6, added some forgotten simulations
2022-05-27 Committing old mechanical design before deleting it
2022-05-27 Finished v0.1 AKL-AV1 for fab
2022-05-27 Cleanup to ground plane under tip
2022-06-11 Small tweaks to AKL-AD4 from design review. Ready for fab.
2022-06-22 Initial version of AKL-PR1 compensation network board
2022-06-24 Missing change from last commit
2022-07-03 kicad6 project files
2022-07-05 Initial version of AKL-PR1 probe head
2022-07-17 Updated AKL-AV1 with v0.4 layout including OPA210 and noise filter
2022-07-17 Updated AKL-PT5 v0.6 design for 450 ohm tip resistor. Shrunk connector area a bit.
2022-07-21 Updated stackup text
2022-08-02 AKL-AD4: rev 0.4 with LM27761 based power stage, 2.5mm shorter, improved heatsinking, removed equalizer
2022-08-03 Mounting foot: updated silkscreen text
2022-08-06 Fixed mounting foot
2022-08-09 Added file missed in last commit
2022-09-24 Updated AKL-PT5 design for v0.9
2022-09-24 Added PT5 simulations for v0.9
2022-10-06 Updated AKL-AV1 to v0.6
2022-11-11 AKL-AV1: updated passives for new filter
2022-11-22 Updated a lot of PT5 sims
2022-11-23 Updated PT5 sims
2022-11-23 Added resistor 3D model
2022-11-23 Initial smpm-test board
2022-12-10 Updated SMPM test design with 0.45mm wide tracks
2022-12-10 Added second ground plane and stitching vias
2022-12-23 Updated beatty line with more stitching vias
2022-12-23 Added Beatty line sims
2022-12-25 Updated ethernet-coupled-probe for v0.2 with correct coupler footprint
2022-12-25 Updated isolation board for gerber export config
2023-05-02 Updated design files for AKL-PT5 v0.11
2023-05-25 Removed a bunch of sims that are no longer applicable to the current design
2023-10-30 Added some old simulations
2024-01-20 Initial version of baset1-inline-probe
2024-02-15 Updated baset1-inline-probe to use matched coupler layout
